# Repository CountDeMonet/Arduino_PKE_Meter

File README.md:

# Arduino_PKE_Meter
Code and models for an arduino based Ghostbusters PKE Meter

GBFans thread: http://www.gbfans.com/forum/viewtopic.php?f=5&t=43258

Video of how the meter looks when finished

https://www.youtube.com/watch?v=xTfZLYqommg

I have also included the eagle cad files that I used to produce an LED board for this project. OshPark is an amazing place to get custom PCB's fabricated and they will take the brd file as is. I ended up using a buck converter to power the servo so the path with the capacitor was no longer needed. That saved some space but the board was already in fab. 

Image of the internals
https://i1.wp.com/vineripesoftware.files.wordpress.com/2017/05/img_20170508_222438829.jpg

I recommend using hitec servo wire if you can get your hands on it for the wings. I printed everything at .3mm resolution with 20% infill. This print requires a lot of support and there is no way around it.

It's based off this model on Thingiverse (https://www.thingiverse.com/thing:700251) I scaled it up to 110%, removed a few buttons to make it easier to use for my son, and created a new battery holder for the 4 AAA's that power it. I decided on an Arduino nano as the brains with a cheap LCD for display. Again, not going for screen accurate but something that will keep a 6-7 year old entertained. I did program in the Ghostbusters 2 LED pattern for the wings.

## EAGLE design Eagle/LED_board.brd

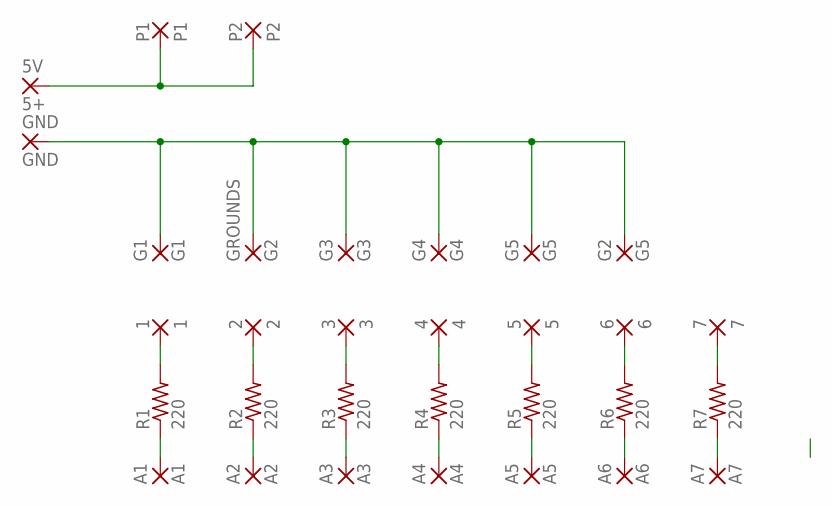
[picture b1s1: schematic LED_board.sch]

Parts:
1: 1; 2,15/1,0
2: 2; 2,15/1,0
3: 3; 2,15/1,0
4: 4; 2,15/1,0
5: 5; 2,15/1,0
5V: 5+; 2,54/1,1
6: 6; 2,15/1,0
7: 7; 2,15/1,0
A1: A1; 2,15/1,0
A2: A2; 2,15/1,0
A3: A3; 2,15/1,0
A4: A4; 2,15/1,0
A5: A5; 2,15/1,0
A6: A6; 2,15/1,0
A7: A7; 2,15/1,0
G1: G1; 2,15/1,0
G2, G5: G5; 2,15/1,0
G3: G3; 2,15/1,0
G4: G4; 2,15/1,0
GND: GND; 2,54/1,1
GROUNDS: G2; 2,15/1,0
P1: P1; 2,15/1,0
P2: P2; 2,15/1,0
R1, R2, R3, R4, R5, R6, R7: 220; 0207/10

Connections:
unnamed: 5V.1, P1.1, P2.1
unnamed: 1.1, R1.2
unnamed: A1.1, R1.1
unnamed: G1.1, G2.1, G3.1, G4.1, G5.1, GND.1, GROUNDS.1
unnamed: 2.1, R2.2
unnamed: A2.1, R2.1
unnamed: A3.1, R3.1
unnamed: 3.1, R3.2
unnamed: 4.1, R4.2
unnamed: A4.1, R4.1
unnamed: A5.1, R5.1
unnamed: 5.1, R5.2
unnamed: 6.1, R6.2
unnamed: A6.1, R6.1
unnamed: A7.1, R7.1
unnamed: 7.1, R7.2

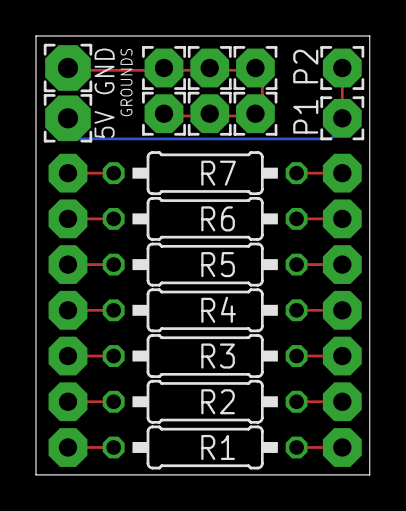
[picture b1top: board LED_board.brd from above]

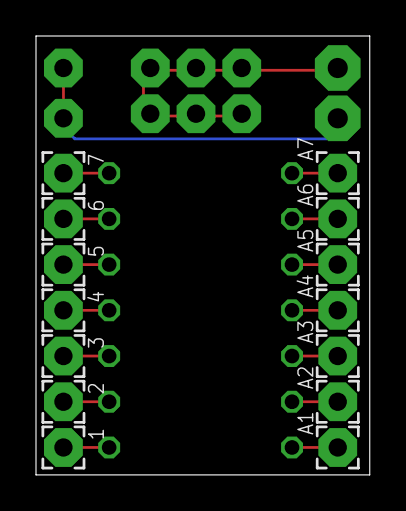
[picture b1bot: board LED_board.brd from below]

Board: 2 copper layers, 18.5 x 24.4 mm, 31 parts (14 on the bottom side), 16 nets.

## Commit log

2017-05-25 change from a press to hold for each state to a toggle
2017-09-11 add required libs used
2017-10-10 cleanup and a fritzing diagram
2018-01-24 Changed the board design so it is cheaper at oshpark and no longer has the unused components
2018-01-24 update schematic
2018-06-11 refactor for mutliple movie support
    Refactors code for looping
    Adds support for both GB1 and GB2 wing light patterns
    Adds setup screens to prompt for which pattern to use and whether to play sounds
2018-06-12 Adds comments for mystery pin
    D2 is acting as VCC for the OLED screen in my current setup running without the buck converter. This adds comments for lines I failed to comment earlier.
2018-08-06 fix errors on front_top and buttons
2018-09-04 buttons were reversed on my build so fixed the code to match the schematic.
2018-09-17 fritzing file for schematic
2020-03-20 experimental one piece versions of the front and back. Printing now will see how well it comes out
